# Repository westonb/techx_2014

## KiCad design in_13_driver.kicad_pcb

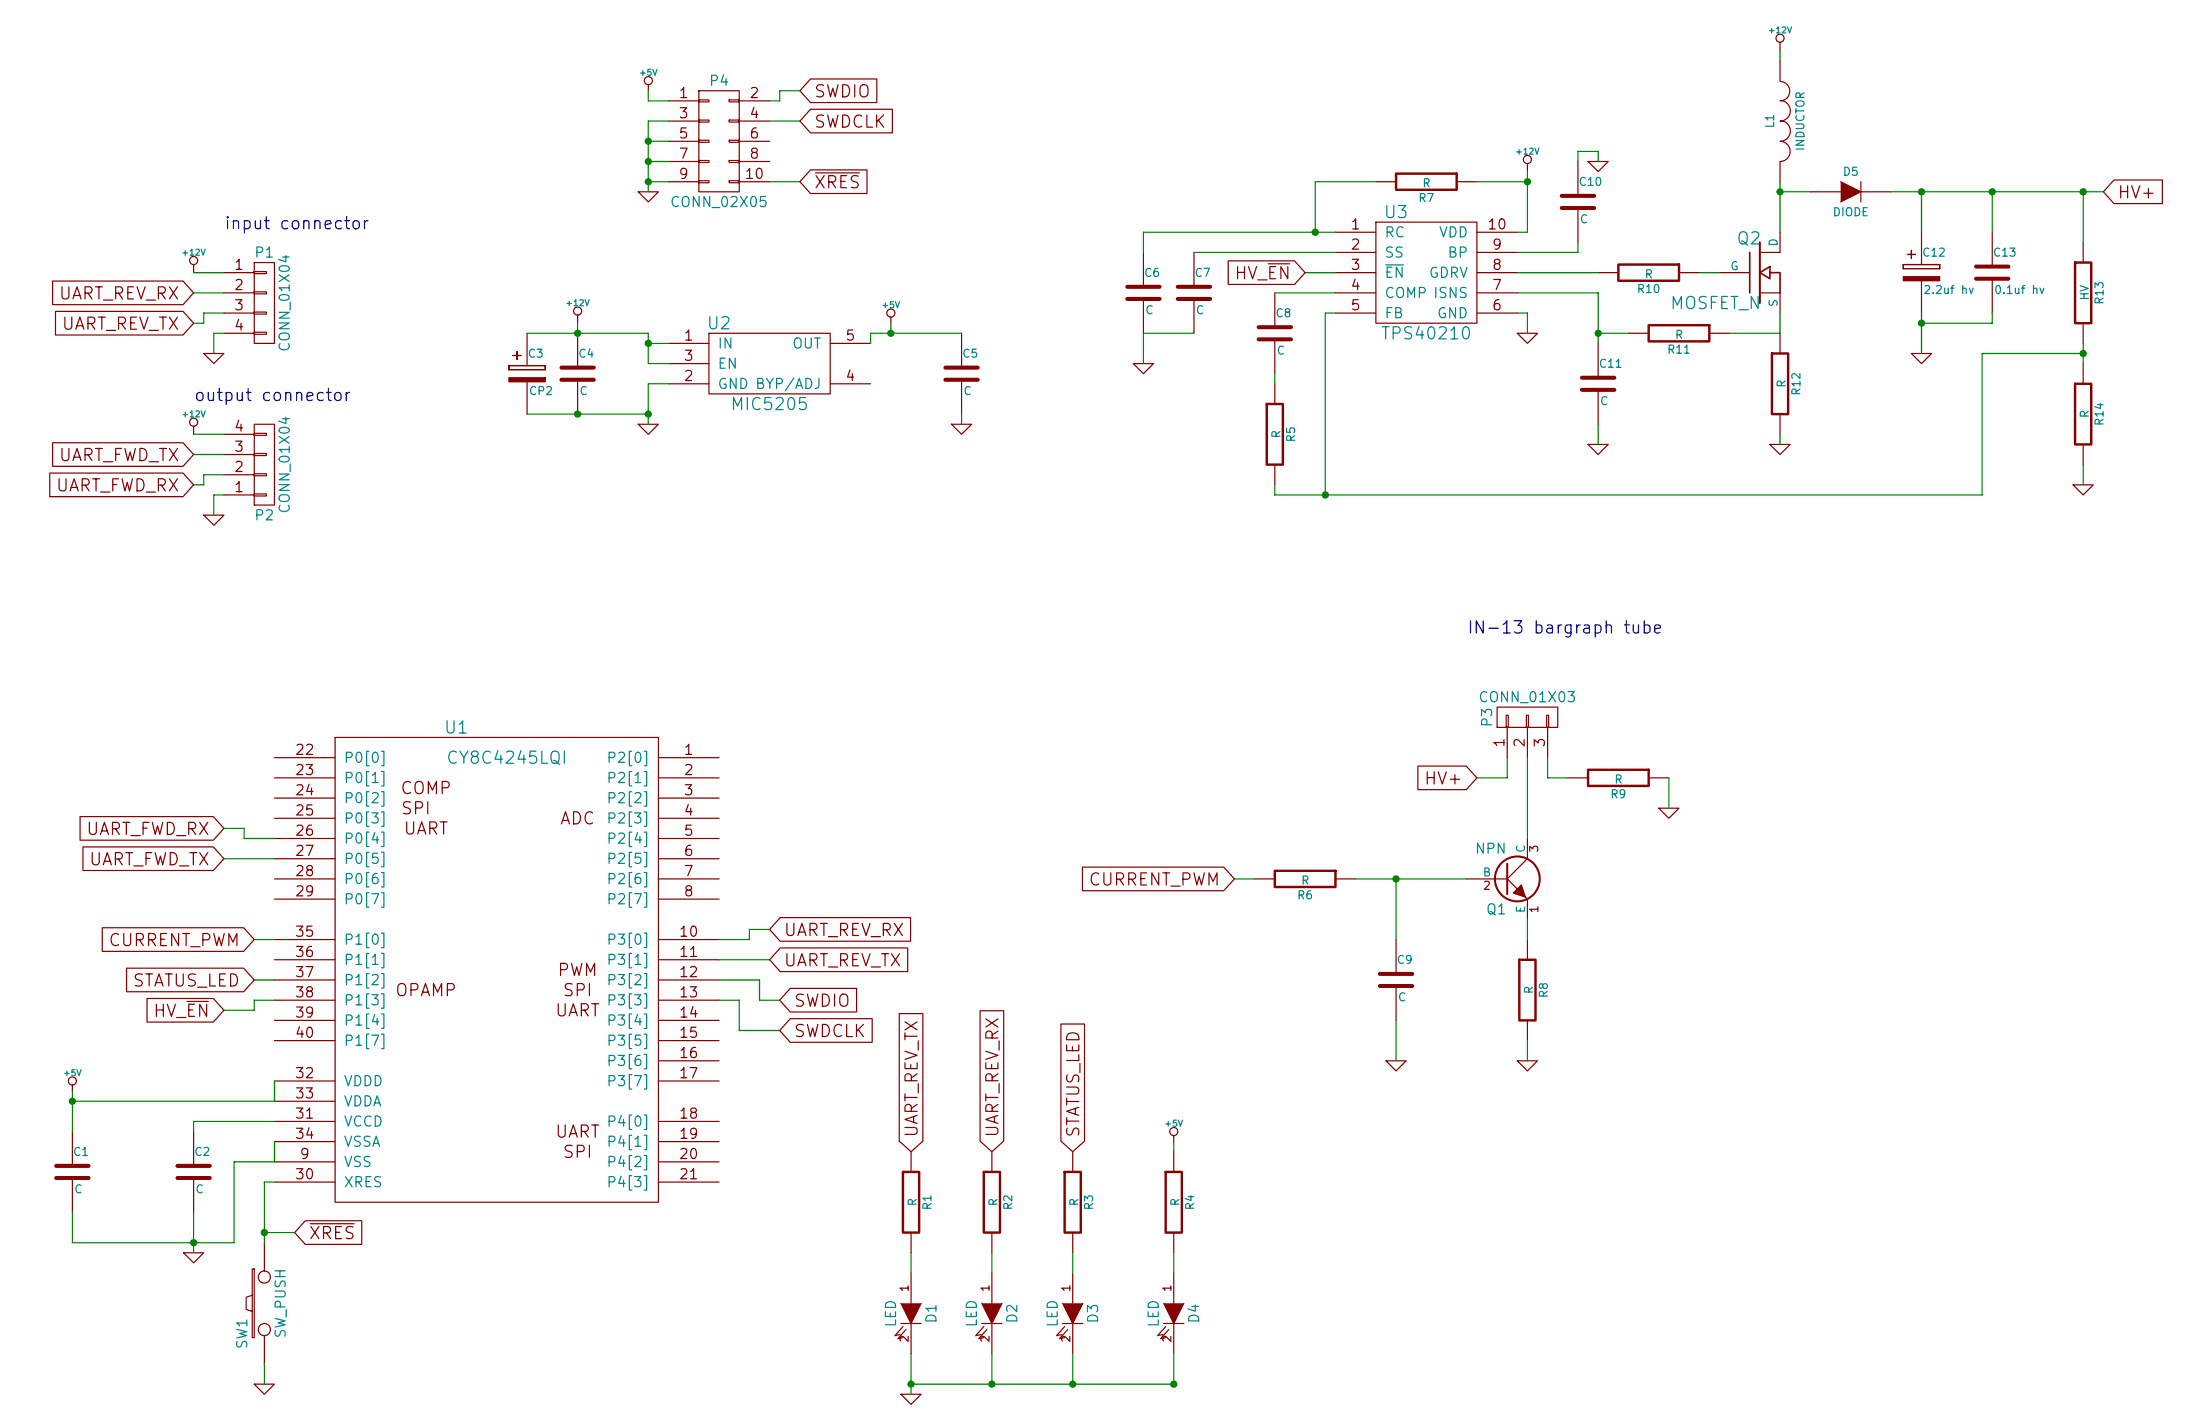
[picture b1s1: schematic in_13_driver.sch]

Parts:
C1, C2, C4, C5, C6, C7, C8, C9, C10, C11: C; SMD-0805
C3: CP2; c_elec_8x6.7
C12: 2.2uf hv; c_elec_10x10
C13: 0.1uf hv; SMD-1206
D1, D2, D3, D4: LED; LED-0805
D5: DIODE; Diode-SMB_Handsoldering
L1: INDUCTOR; LPS8045
P1, P2: CONN_01X04; Pin_Header_Straight_1x04
P3: CONN_01X03; Pin_Header_Straight_1x03
P4: CONN_02X05; smd_header_10
Q1: NPN; SOT-223-NPN-BCE
Q2: MOSFET_N; DPAK-3_GDS
R1, R2, R3, R4, R5, R6, R7, R8, R9, R10, R11, R14: R; SMD-0805
R12: R; SMD-1206
R13: HV; SMD-1206
SW1: SW_PUSH; button-5mm
U1: CY8C4245LQI; QFN-40
U2: MIC5205; SOT-23-5
U3: TPS40210; 10-MSOP

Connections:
+5V: C1.1, C5.1, P4.1, R4.1, U1.32 (VDDD), U1.33 (VDDA), U2.5 (OUT)
+12V: C3.1, C4.1, L1.1, P1.1, P2.4, R7.1, U2.1 (IN), U2.3 (EN), U3.10 (VDD)
CURRENT_PWM: R6.2, U1.35 (P1[0])
GND: C1.2, C2.2, C3.2, C4.2, C5.2, C6.2, C7.2, C9.2, C10.1, C11.2, C12.2, C13.2, D1.2 (K), D2.2 (K), D3.2 (K), D4.2 (K), P1.4, P2.1, P4.3, P4.5, P4.7, P4.9, R8.2, R9.1, R12.2, R14.2, SW1.2, U1.9 (VSS), U1.34 (VSSA), U2.2 (GND), U3.6 (GND), U3.11 (GND_PAD)
HV+: C12.1, C13.1, D5.2 (K), P3.1, R13.1
HV_~EN~: U1.38 (P1[3]), U3.3 (~EN~)
unnamed: C2.1, U1.31 (VCCD)
unnamed: C6.1, R7.2, U3.1 (RC)
unnamed: C7.1, U3.2 (SS)
unnamed: C8.1, U3.4 (COMP)
unnamed: C8.2, R5.1
unnamed: C9.1, Q1.2 (B), R6.1
unnamed: C10.2, U3.9 (BP)
unnamed: C11.1, R11.2, U3.7 (ISNS)
unnamed: D1.1 (A), R1.2
unnamed: D2.1 (A), R2.2
unnamed: D3.1 (A), R3.2
unnamed: D4.1 (A), R4.2
unnamed: D5.1 (A), L1.2, Q2.D
unnamed: P3.2, Q1.3 (C)
unnamed: P3.3, R9.2
unnamed: Q1.1 (E), R8.1
unnamed: Q2.G, R10.1
unnamed: Q2.S, R11.1, R12.1
unnamed: R10.2, U3.8 (GDRV)
unnamed: R5.2, R13.2, R14.1, U3.5 (FB)
STATUS_LED: R3.1, U1.37 (P1[2])
SWDCLK: P4.4, U1.13 (P3[3])
SWDIO: P4.2, U1.12 (P3[2])
UART_FWD_RX: P2.2, U1.26 (P0[4])
UART_FWD_TX: P2.3, U1.27 (P0[5])
UART_REV_RX: P1.2, R2.1, U1.10 (P3[0])
UART_REV_TX: P1.3, R1.1, U1.11 (P3[1])
~XRES~: P4.10, SW1.1, U1.30 (XRES)

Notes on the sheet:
input connector
output connector
IN-13 bargraph tube

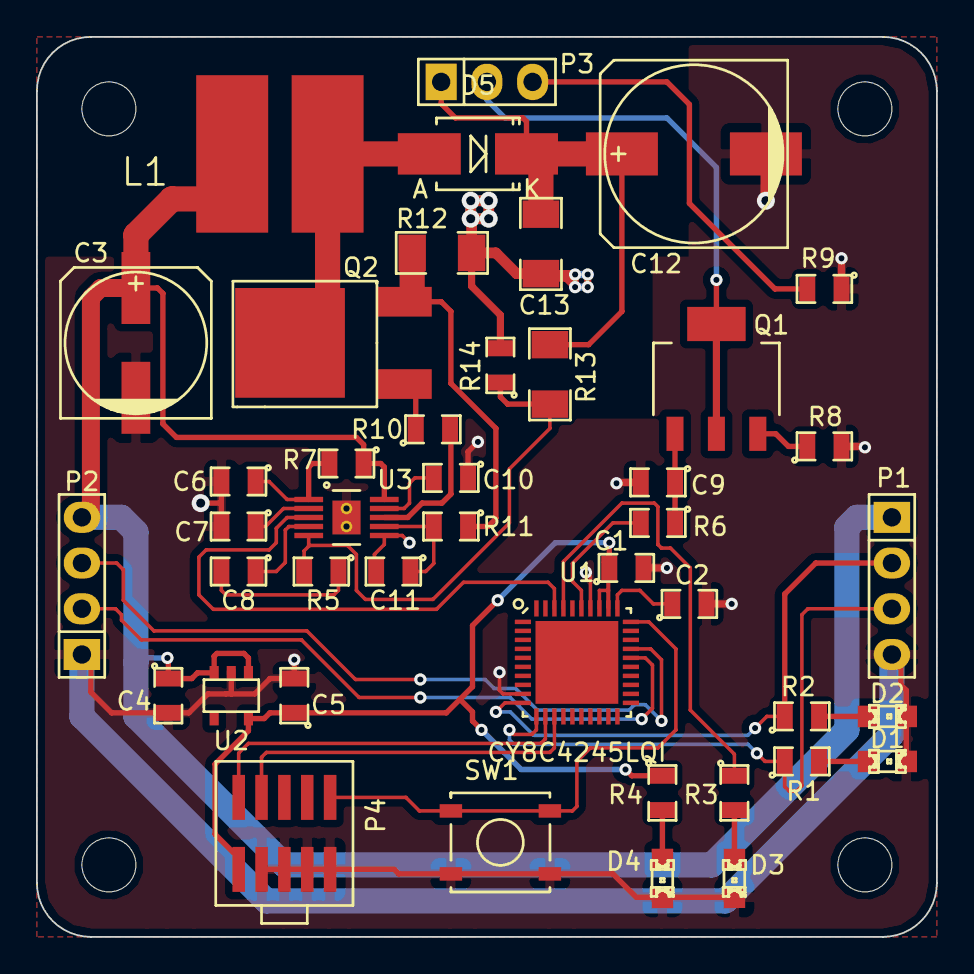
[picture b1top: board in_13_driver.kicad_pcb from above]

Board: 2 copper layers, 50.0 x 50.0 mm, 47 parts (0 on the bottom side), 34 nets.

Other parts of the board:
MountingHole_3mm, MountingHole_3mm#2, MountingHole_3mm#3, MountingHole_3mm#4: VAL**; MountingHole_3mm
